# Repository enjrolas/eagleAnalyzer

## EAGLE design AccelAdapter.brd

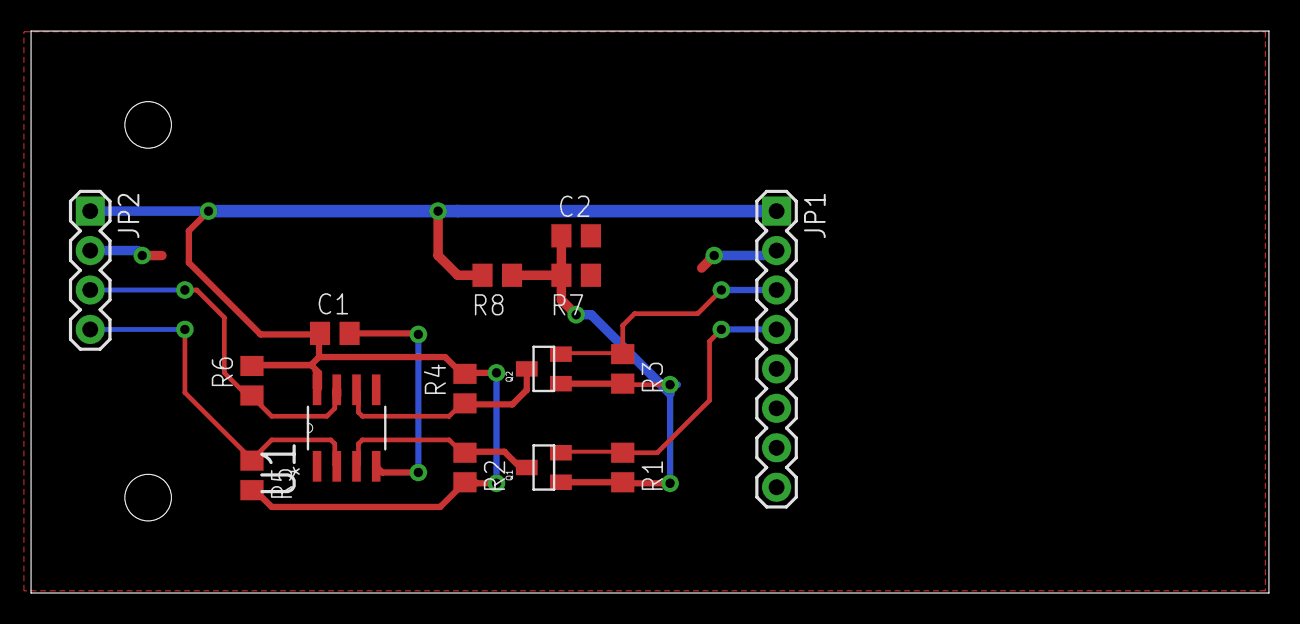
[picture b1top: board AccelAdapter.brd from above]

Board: 2 copper layers, 79.7 x 36.2 mm, 15 parts (0 on the bottom side), 9 nets.

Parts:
C1, C2: .1uF; C0805
JP1: Accel; 1X08
JP2: I2CExt; 1X04
Q1, Q2: MOSFET-NCHANNELBSS138; SOT23
R1, R2, R3, R4: 10k; R0805
R5, R6: 470R; R0805
R7: 330R; R0805
R8: 169R; R0805
U1: P82B715D; SOIC127P600X175-8N

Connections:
+3V3: C2.1, Q1.1, Q2.1, R1.2, R3.2, R7.2, R8.1
+5V: C1.1, JP1.1, JP2.1, R2.2, R4.2, R5.2, R6.2, R8.2, U1.8
GND: C1.2, C2.2, JP1.2, JP2.2, R7.1, U1.4
HSCL: Q2.3, R4.1, U1.6
HSDA: Q1.3, R2.1, U1.3
LCL: JP2.3, R6.1, U1.7
LDA: JP2.4, R5.1, U1.2
SCL: JP1.3, Q2.2, R3.1
SDA: JP1.4, Q1.2, R1.1

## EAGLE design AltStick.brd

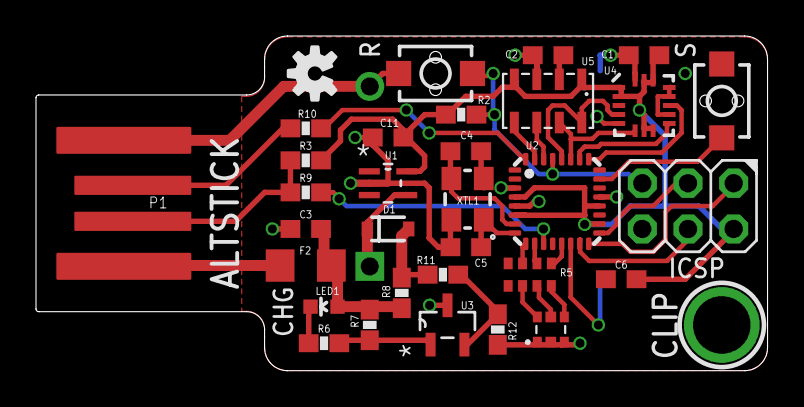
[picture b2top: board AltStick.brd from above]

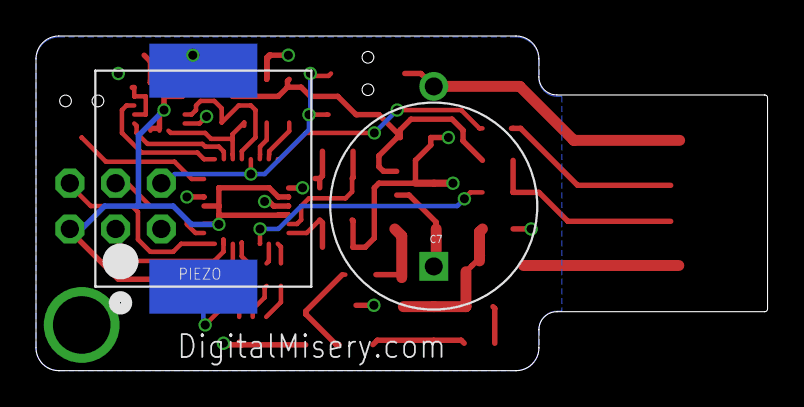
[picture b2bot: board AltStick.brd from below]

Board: 2 copper layers, 40.6 x 18.6 mm, 34 parts (2 on the bottom side), 34 nets.

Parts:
C1, C2, C6: 100nF; C0603
C3, C11: 1uF; C0603
C4, C5: 18pF; C0603
C7: 0.47F; KR-H11.5
D1: SOD-323
F2: R1206
ICSP: ICSP; 2X03
LED1: Green; LED-0603
LED2: RGBLEDSMT; 19-337
P1: USBPCB; USB-A-PCB
PIEZO: BUZZERSMD12X12; BUZZER-12X12-SMT
R2: 10k; 0603-RES
R3: 1.5k; 0603-RES
R5: 0603-ARV
R6: 1K; 0603-RES
R7: 1k; 0603-RES
R8: 20; 0603-RES
R9, R10: 30; 0603-RES
R11: 95k; 0603-RES
R12: 100k; 0603-RES
S1: RESET; TACTILE_SWITCH_SMD_2PIN_TINY
S2: BUTTON; TACTILE_SWITCH_SMD_2PIN_TINY
U1: TPS71533DCKR; SOT65P210X110-5N
U2: ATMEGA168MLF; MLF32
U3: TL431CDBZR; SOT95P237X112-3N
U4: LIS331; LGA16-3MM
U5: MPL3115A2LGA8; LGA8
U$2: OSHW-LOGOS; OSHW-LOGO-S
XTL1: 12MHz; CRYSTAL-SMD-3X2

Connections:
3.3V: C1.1, C6.1, C11.1, ICSP.2, R2.2, R3.1, U1.5, U2.4, U2.6, U2.18, U2.20, U4.1, U4.7, U4.8, U4.14, U4.15, U5.1, U5.4
ACC_I1: U2.25, U4.11
ACC_I2: U2.26, U4.9
ALT_I1: U2.30, U5.6
ALT_I2: U2.31, U5.5
D+: P1.USB_P, R10.2
D-: P1.USB_M, R3.2, R9.2
GND: C1.2, C2.2, C3.2, C4.2, C5.2, C6.2, C7.2, C11.2, ICSP.6, LED2.1, LED2.2, LED2.3, P1.GND, PIEZO.1, R12.1, S1.1, S2.2, U1.2, U2.3, U2.5, U2.21, U3.3, U4.5, U4.10, U4.12, U4.13, U4.16, U5.3, XTL1.2, XTL1.4
LED1: R5.7, U2.9
LED2: R5.6, U2.10
LED3: R5.5, U2.13
MISO: ICSP.1, U2.16
MOSI: ICSP.4, U2.15
unnamed: S2.1, U2.23
unnamed: F2.1, P1.5V
unnamed: LED2.4, R5.2
unnamed: LED2.5, R5.3
unnamed: LED1.C, R6.2
unnamed: R6.1, R7.1, U3.1
unnamed: R11.1, R12.2, U3.2
unnamed: C7.1, D1.1, U1.4
unnamed: D1.2, R8.2, R11.2
unnamed: C4.1, U2.7, XTL1.3
unnamed: C5.1, U2.8, XTL1.1
unnamed: LED2.6, R5.4
unnamed: C2.1, U5.2
PIEZO: PIEZO.2, U2.14
RD+: R10.1, U2.32
RD-: R9.1, U2.11
RESET: ICSP.5, R2.1, S1.2, U2.29
SCK: ICSP.3, U2.17
SCL: U2.28, U4.4, U5.8
SDA: U2.27, U4.6, U5.7
USBVCC: C3.1, F2.2, LED1.A, R7.2, R8.1

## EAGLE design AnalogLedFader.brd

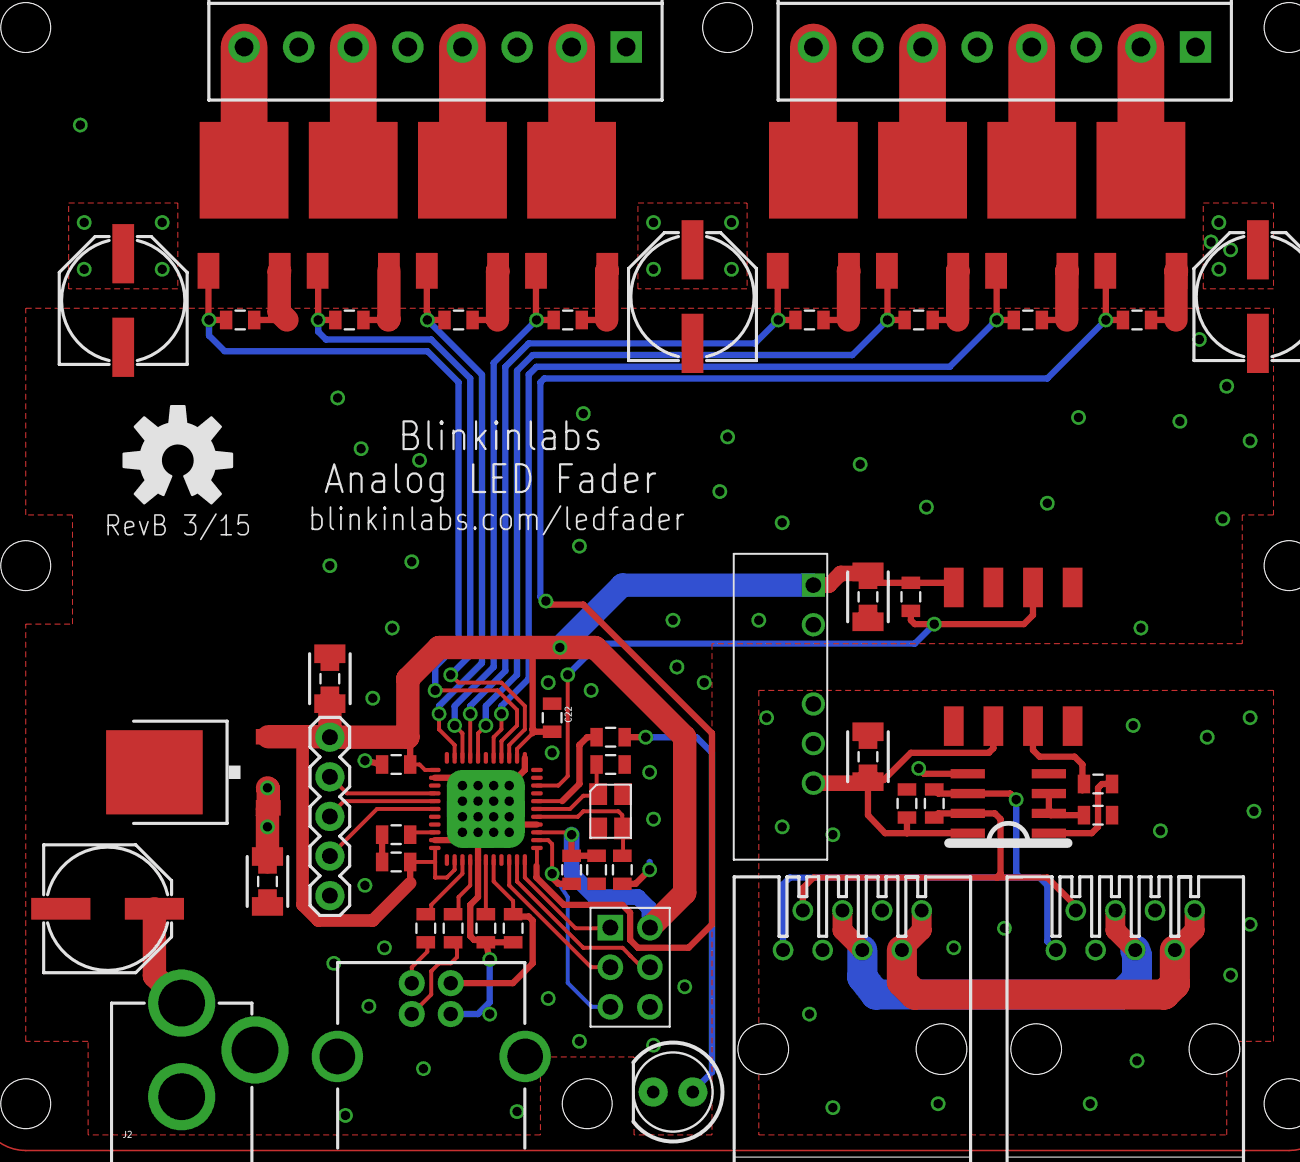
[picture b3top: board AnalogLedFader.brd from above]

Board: 2 copper layers, 62 parts (0 on the bottom side), 46 nets.

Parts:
C1, C2: 16pf; 0805
C3, C5, C6, C7, C12, C22: 100nF; 0805
C4, C8, C15: 1uF; 0805
C9: 4.7uF; 0805
C10: 10uF; 0805
C11: .3uF; 0805
C13: .3uF; 1210
C14: 100nF; 1210
C16: 4.7uF; 1210
C17: 10uF; 1210
C23, C24, C25, C26: PANASONIC_E
IC2: 7805DT; TO252
J1, J3: RS485; 520426-4
J2: POWER_JACKPTH; POWER_JACK_PTH
JP2, JP3: SCREWTERMINAL-3.5MM-8
JP6: 1X05
LED1: LED5MM
Q1: 16MHz 10ppm; XS3225
R1: 180 DNP; 0805
R2: 10k; 0805
R3, R4, R7, R9, R10, R13, R14, R15, R16: 10K; 0805
R5, R6: 22; 0805
R8, R11, R12: 470; 0805
U1: ARDUINO_LEONARDO-REV3B_SMARTPRJ_ATMEGA32U4-XUMU; ARDUINO_LEONARDO-REV3B_SMARTPRJ_QFN44ML7X7
U2: SN75176ASOIC; SO08
U$1, U$3, U$4, U$5, U$6, U$7, U$8, U$9: N_MOSFET; TO252
U$2: 2X3HEADER
U$10: DC_DC_ISOLATED_0505; IB_XLS-1W
U$12: 6N137; 8_SOIC
U$13: OSHW-LOGO-L
X1: USBPTH; USB-B-PTH

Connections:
5V_ISO: C7.2, C10.2, C17.1, U2.8, U$10.P$5, U$12.P$2
A1: JP6.2, U1.37
A2: JP6.3, U1.38
A3: JP6.4, U1.39
CONNECT_ME: R2.1, U2.2, U2.3
GND: C1.1, C2.1, C3.1, C4.1, C5.1, C6.1, C8.1, C9.1, C11.1, C12.1, C13.2, C14.2, C15.1, C16.2, C22.1, C23.-, C24.-, C25.-, C26.-, IC2.3, J2.GND, J2.GNDBREAK, JP6.5, LED1.K, R3.1, R7.1, R9.1, R10.1, R13.1, R14.1, R15.1, R16.1, U1.5, U1.15, U1.23, U1.35, U1.43, U1.PAD@1, U1.PAD@2, U1.PAD@3, U1.PAD@4, U1.PAD@5, U1.PAD@6, U1.PAD@7, U1.PAD@8, U1.PAD@9, U1.PAD@10, U1.PAD@11, U1.PAD@12, U1.PAD@13, U1.PAD@14, U1.PAD@15, U1.PAD@16, U$1.P$2, U$2.P$6, U$3.P$2, U$4.P$2, U$5.P$2, U$6.P$2, U$7.P$2, U$8.P$2, U$9.P$2, U$10.P$2, U$12.P$5, X1.GND
GND_ISO: C7.1, C10.1, C17.2, J1.7, J1.8, J3.7, J3.8, R2.2, U2.5, U$10.P$3, U$10.P$4
LED: R8.2, U1.18
MISO: U1.11, U$2.P$1
MOSI: U1.10, U$2.P$4
unnamed: R6.1, X1.D-
unnamed: C1.2, Q1.P$3, U1.16
unnamed: R5.1, X1.D+
unnamed: R5.2, U1.4
unnamed: C2.2, Q1.P$1, U1.17
unnamed: R6.2, U1.3
unnamed: LED1.A, R8.1
unnamed: C4.2, U1.6
unnamed: C8.2, U1.7, X1.VBUS
unnamed: C15.2, U1.42
unnamed: R11.1, U$12.P$3
OUT0: JP2.2, U$1.P$3
OUT1: JP2.4, U$3.P$3
OUT2: JP2.6, U$4.P$3
OUT3: JP2.8, U$5.P$3
OUT4: JP3.2, U$6.P$3
OUT5: JP3.4, U$7.P$3
OUT6: JP3.6, U$8.P$3
OUT7: JP3.8, U$9.P$3
PWM0: R10.2, U1.12, U$1.P$1
PWM1: R9.2, U1.27, U$3.P$1
PWM2: R7.2, U1.29, U$4.P$1
PWM3: R3.2, U1.30, U$5.P$1
PWM4: R13.2, U1.31, U$6.P$1
PWM5: R14.2, U1.32, U$7.P$1
PWM6: R15.2, U1.25, U$8.P$1
PWM7: R16.2, U1.26, U$9.P$1
RESET: R4.1, U1.13, U$2.P$5
RS485A: J1.1, J3.1, R1.1, U2.6
RS485B: J1.2, J3.2, R1.2, U2.7
RX: R12.1, U1.20, U$12.P$6
RX_ISO: R11.2, U2.1
SCK: U1.9, U$2.P$3
VCC: C3.2, C5.2, C6.2, C9.2, C12.2, C14.1, C16.1, C22.2, IC2.2, JP6.1, R4.2, R12.2, U1.2, U1.14, U1.24, U1.34, U1.44, U$2.P$2, U$10.P$1, U$12.P$8
VMOT: J1.4, J1.5, J3.4, J3.5
V_IN: C11.2, C13.1, C23.+, C24.+, C25.+, C26.+, IC2.1, J2.PWR, JP2.1, JP2.3, JP2.5, JP2.7, JP3.1, JP3.3, JP3.5, JP3.7

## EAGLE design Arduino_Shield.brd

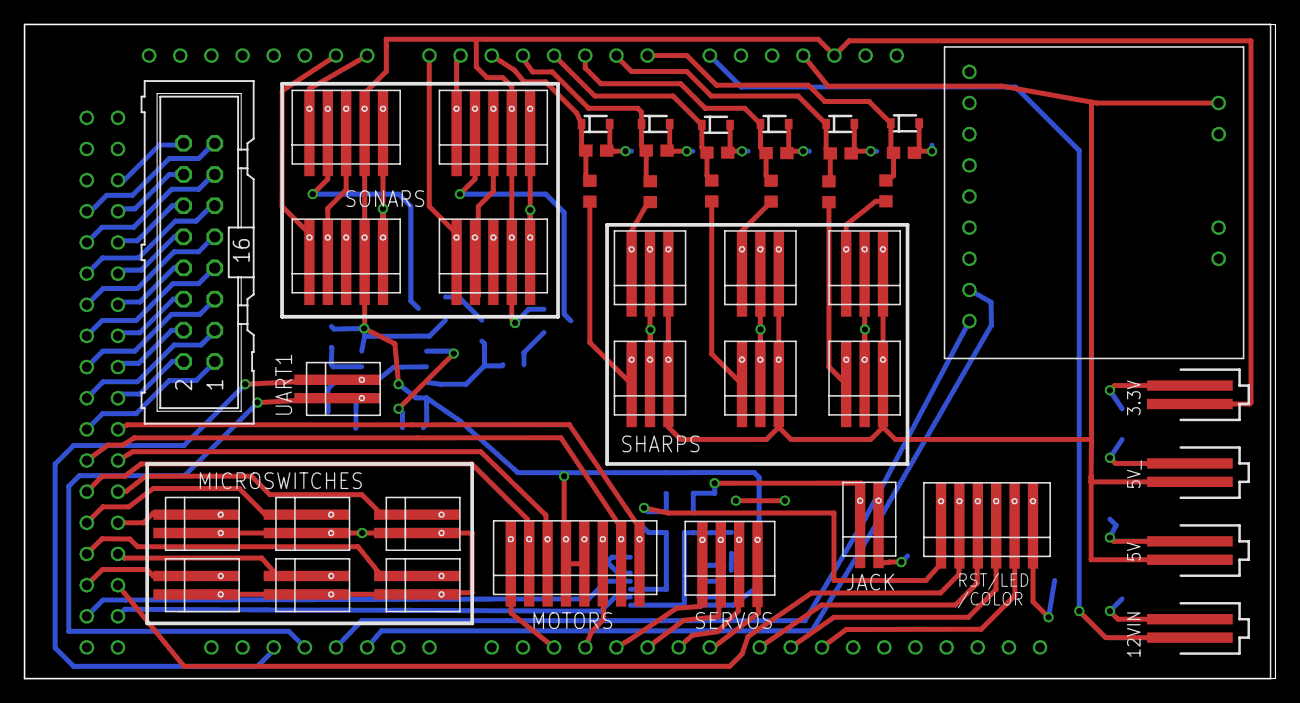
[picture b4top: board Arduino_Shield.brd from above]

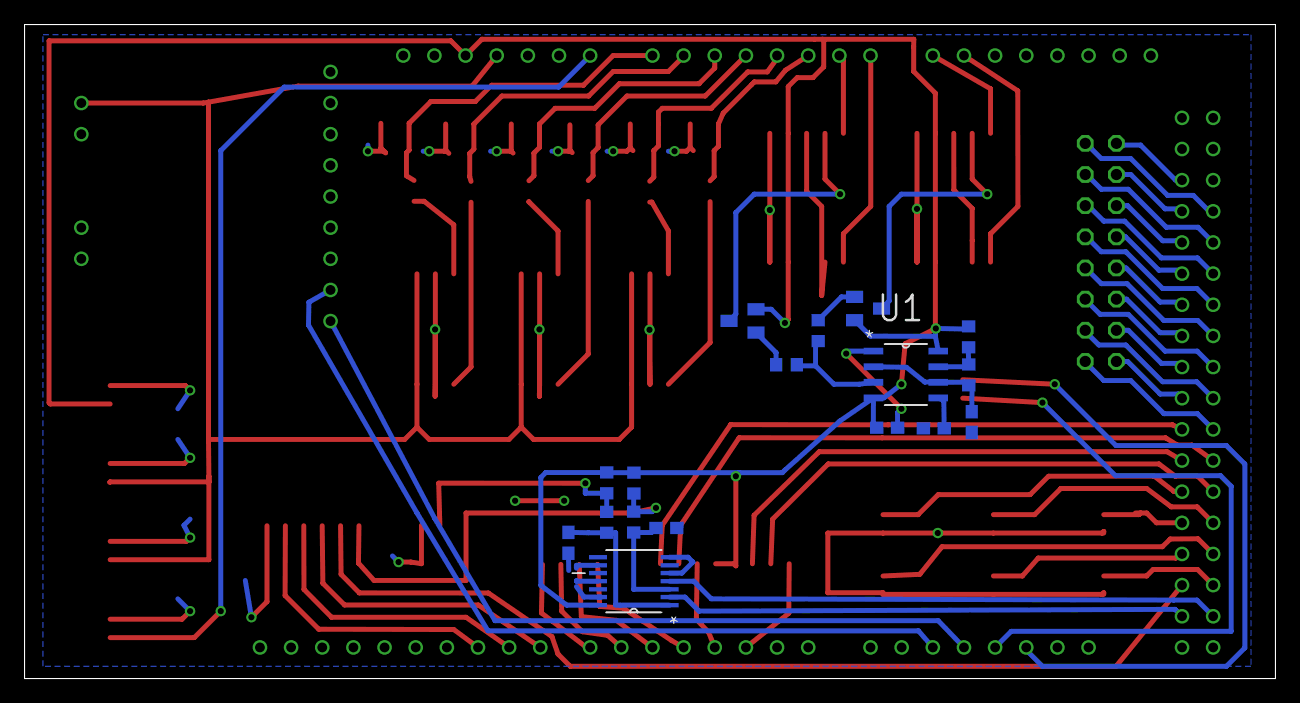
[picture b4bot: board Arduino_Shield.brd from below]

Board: 2 copper layers, 102.0 x 53.3 mm, 63 parts (17 on the bottom side), 76 nets.

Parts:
3.3V, 5V, 5V_, 12VIN: 87438-02
C1, C2, C4, C5, C6, C7, C8, C9: 0.1uF; C0603
C3: 1uF; C0603
C10, C11: 10uF; C0603
FPGA: ML16
JACK: 87437-0243
MOTORS: 87437-0843
Q1, Q2: BC857B; SOT23
R1, R2, R3, R4, R5, R6, R7, R10, R11, R12: 10K; R0603
R8, R9: 1K; R0603
RA: 330K; R0603
RB: 3.3K; R0603
RST/LED/COLOR: 87437-0643
SERVOS: 87437-0443
SHARP1, SHARP2, SHARP3, SHARP4, SHARP5, SHARP6: 87437-0343
SONAR_BL: 87437-0543
SONAR_BR: 87437-0543
SONAR_FL: 87437-0543
SONAR_FR: 87437-0543
U1: TLC555; SOIC127P600X175-8N
U2: SN74HC14PW; SOP65P640X120-14N
U$1: ARDUINO-DUE
U$2, U$3, U$4, U$5, U$6, U$7: ZENER_3.3V; SOD-323
UART1: 87437-0243
UM6: UM6
USW1, USW2, USW3, USW4, USW5, USW6: 87437-0243

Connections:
3.3VCC: 3.3V.1, C8.1, MOTORS.P$4, MOTORS.P$5, Q1.2, Q2.2, R7.2, R10.2, RA.2, SONAR_BL.P$4, SONAR_BR.P$4, SONAR_FL.P$4, SONAR_FR.P$4, U1.4, U1.8, U2.14, U$1.3.3V
5VCC: 5V.1, 5V_.1, SHARP1.P$3, SHARP2.P$3, SHARP3.P$3, SHARP4.P$3, SHARP5.P$3, SHARP6.P$3, U$1.5V3, UM6.P$10
12VIN: 12VIN.1, U$1.VIN
COLOR: RST/LED/COLOR.P$2, U$1.24
GND: 3.3V.2, 5V.2, 5V_.2, 12VIN.2, C1.1, C2.2, C3.2, C4.1, C5.1, C6.1, C7.1, C8.2, C9.1, C10.2, C11.2, JACK.P$2, RST/LED/COLOR.P$6, SHARP1.P$2, SHARP2.P$2, SHARP3.P$2, SHARP4.P$2, SHARP5.P$2, SHARP6.P$2, SONAR_BL.P$5, SONAR_BR.P$5, SONAR_FL.P$5, SONAR_FR.P$5, U1.1, U2.5, U2.7, U2.9, U2.11, U2.13, U$1.GND4, U$2.2, U$3.2, U$4.2, U$5.2, U$6.2, U$7.2, UM6.P$11, USW1.P$2, USW2.P$2, USW3.P$2, USW4.P$2, USW5.P$2, USW6.P$2
MOTOR1_BREAK: MOTORS.P$3, U$1.32
MOTOR1_DIR: MOTORS.P$2, U$1.31
MOTOR1_PWM: MOTORS.P$1, U$1.PWM2
MOTOR2_BREAK: MOTORS.P$8, U$1.34
MOTOR2_DIR: MOTORS.P$7, U$1.33
MOTOR2_PWM: MOTORS.P$6, U$1.PWM3
unnamed: RST/LED/COLOR.P$3, U$1.PWM8
unnamed: SERVOS.P$1, U$1.PWM4
unnamed: SERVOS.P$2, U$1.PWM5
unnamed: SERVOS.P$3, U$1.PWM6
unnamed: SERVOS.P$4, U$1.PWM7
unnamed: U$1.TX1, UART1.P$2
unnamed: U$1.RX1, UART1.P$1
unnamed: U2.2, U$1.22
unnamed: RST/LED/COLOR.P$4, U$1.PWM9
unnamed: RST/LED/COLOR.P$5, U$1.PWM10
unnamed: U2.4, U$1.23
unnamed: JACK.P$1, R7.1, R8.2
unnamed: C3.1, RB.1, U1.2, U1.6
unnamed: C2.1, U1.5
unnamed: RA.1, RB.2, U1.7
unnamed: R11.2, R12.2, U1.3
unnamed: Q2.1, R12.1
unnamed: Q1.1, R11.1
unnamed: SONAR_FL.P$3, SONAR_FR.P$2
unnamed: SONAR_BL.P$3, SONAR_BR.P$2
unnamed: FPGA.1, U$1.35
unnamed: Q1.3, SONAR_FL.P$2
unnamed: Q2.3, SONAR_BL.P$2
unnamed: FPGA.2, U$1.36
unnamed: FPGA.3, U$1.37
unnamed: FPGA.4, U$1.38
unnamed: FPGA.5, U$1.39
unnamed: FPGA.6, U$1.40
unnamed: FPGA.7, U$1.41
unnamed: FPGA.8, U$1.42
unnamed: FPGA.9, U$1.43
unnamed: FPGA.10, U$1.44
unnamed: FPGA.11, U$1.45
unnamed: FPGA.12, U$1.46
unnamed: FPGA.13, U$1.47
unnamed: FPGA.14, U$1.48
unnamed: FPGA.15, U$1.49
unnamed: FPGA.16, U$1.50
unnamed: R5.1, SHARP2.P$1
unnamed: R4.1, SHARP3.P$1
unnamed: R3.1, SHARP4.P$1
unnamed: R2.1, SHARP5.P$1
unnamed: R1.1, SHARP6.P$1
unnamed: C10.1, R8.1, U2.1
unnamed: R6.1, SHARP1.P$1
unnamed: C11.1, R9.1, U2.3
RST: R9.2, R10.1, RST/LED/COLOR.P$1
SHARP1: C1.2, R6.2, U$1.A0, U$2.1
SHARP2: C4.2, R5.2, U$1.A1, U$3.1
SHARP3: C5.2, R4.2, U$1.A2, U$4.1
SHARP4: C6.2, R3.2, U$1.A3, U$5.1
SHARP5: C7.2, R2.2, U$1.A4, U$6.1
SHARP6: C9.2, R1.2, U$1.A5, U$7.1
SONAR_BL: SONAR_BL.P$1, U$1.A8
SONAR_BR: SONAR_BR.P$1, U$1.A9
SONAR_FL: SONAR_FL.P$1, U$1.A6
SONAR_FR: SONAR_FR.P$1, U$1.A7
UM6_RX: U$1.TX2, UM6.P$2
UM6_TX: U$1.RX2, UM6.P$1
USW1: U$1.25, USW1.P$1
USW2: U$1.26, USW2.P$1
USW3: U$1.27, USW3.P$1
USW4: U$1.28, USW4.P$1
USW5: U$1.29, USW5.P$1
USW6: U$1.30, USW6.P$1

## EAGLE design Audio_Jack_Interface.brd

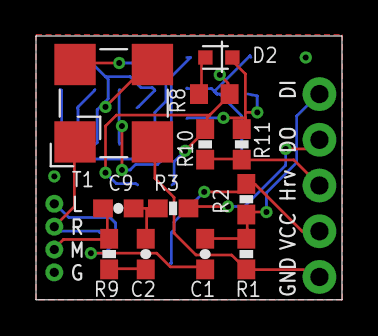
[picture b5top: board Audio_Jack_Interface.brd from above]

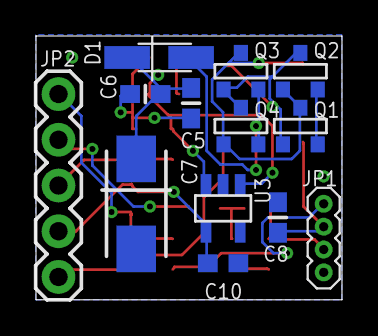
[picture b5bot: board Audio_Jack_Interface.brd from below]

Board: 2 copper layers, 17.0 x 14.7 mm, 25 parts (13 on the bottom side), 14 nets.

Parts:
C1: 0.1 uF; 0603-CAP
C2: 4.7nF; 0603-CAP
C5: 1uF; C0603
C6: 10uF; C0603
C7: CP6032; CT6032
C8: 2.2u; C0603
C9: 10uF; 0603-CAP
C10: 10u; C0603
D1: DIODE; MINIMELF
D2: LED-0603
JP1: 1X04-1.27MM
JP2: 1X05
Q1, Q2, Q3, Q4: SOT-23
R1, R2: 100k; 0603-RES
R3: 10k; 0603-RES
R8: 698; R0603
R9: 1k; 0603-RES
R10: 3M; 0603-RES
R11: 1M; 0603-RES
T1: LPR6235
U3: MIC5231; SOT23-5

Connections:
GND: C2.2, C5.2, C6.2, C7.-, C8.2, C10.2, D2.C, JP1.1, JP2.1, Q1.2, Q2.2, R1.1, R9.2, R11.1, T1.2, U3.2
LEFT: C1.1, JP1.4
MIC: C9.2, JP1.2, R9.1
unnamed: C1.2, JP2.5, R1.2, R2.1
unnamed: JP2.3, R10.1, R11.2
unnamed: JP2.4, R3.2
unnamed: Q1.1, Q2.3, Q3.1, Q4.3, T1.4
unnamed: Q1.3, Q2.1, Q3.3, Q4.1, T1.3
unnamed: D2.A, R8.2
unnamed: C2.1, C9.1, R3.1
unnamed: D1.A, Q3.2, Q4.2
RIGHT: C8.1, JP1.3, T1.1
VCC: C10.1, JP2.2, R2.2, U3.4
VHARVEST: C5.1, C6.1, C7.+, D1.C, R8.1, R10.2, U3.1, U3.3

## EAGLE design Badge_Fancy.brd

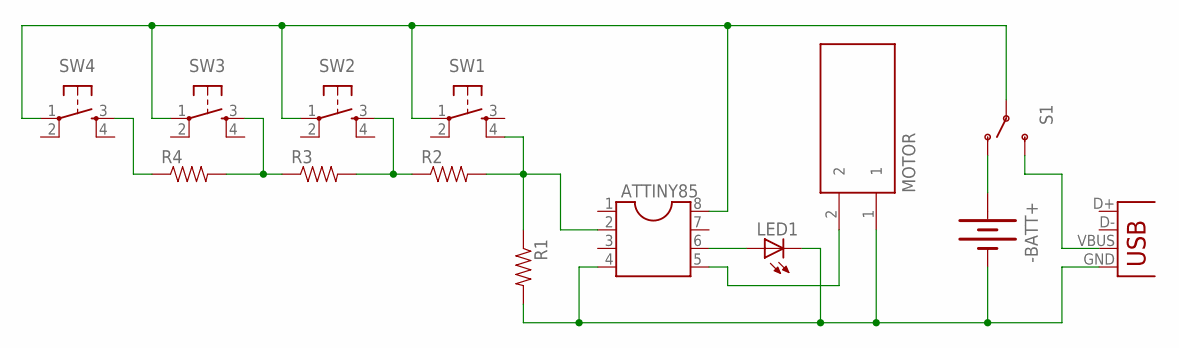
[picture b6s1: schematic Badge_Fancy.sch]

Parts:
-BATT+: BATTERY245MM; BATTCON_245MM
ATTINY85: DIL8S; SOCKET-08
LED1: LEDCHIPLED_0805; CHIPLED_0805
MOTOR: VIB-MOTOR
R1, R2, R3, R4: RESISTOR2010; R2010
S1: SWITCH-SPSTSMD; AYZ0202
SW1, SW2, SW3, SW4: TAC_SWITCHPTH; TACTILE-PTH
X2: USBSMD; USB-MINIB

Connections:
+3V: ATTINY85.8, S1.2, SW1.1, SW2.1, SW3.1, SW4.1
GND: -BATT+.2 (-), ATTINY85.4, LED1.C, MOTOR.1, R1.2, X2.GND
unnamed: ATTINY85.5, MOTOR.2
unnamed: -BATT+.1 (+), S1.1 (O)
unnamed: S1.3 (S), X2.VBUS
unnamed: ATTINY85.2, R1.1, R2.2, SW1.4
unnamed: ATTINY85.6, LED1.A
unnamed: R4.1, SW4.3
unnamed: R3.1, R4.2, SW3.3
unnamed: R2.1, R3.2, SW2.3

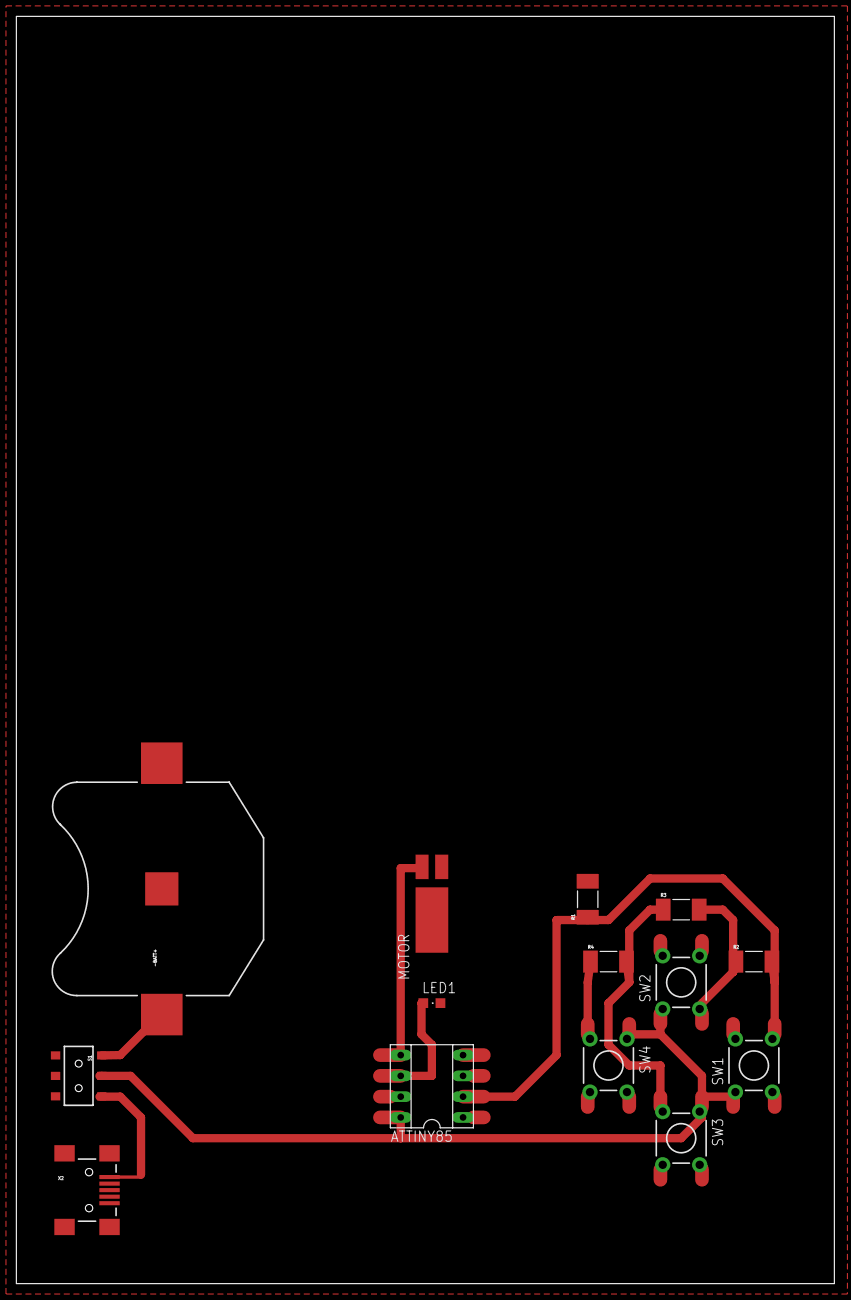
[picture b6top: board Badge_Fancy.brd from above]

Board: 2 copper layers, 100.0 x 154.9 mm, 14 parts (0 on the bottom side), 10 nets.

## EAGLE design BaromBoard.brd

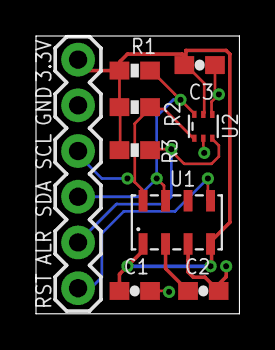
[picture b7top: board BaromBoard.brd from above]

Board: 2 copper layers, 11.3 x 15.4 mm, 9 parts (0 on the bottom side), 7 nets.

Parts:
C1, C2, C3: 1uF; 0603-CAP
JP1: 1X06
R1, R2, R3: 0603-RES
TMP102: TMP102; SOT563
U1: MPL115A; LGA8

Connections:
3.3V: C1.1, C3.1, JP1.1, R1.2, R2.2, R3.1, TMP102.5, U1.1, U1.4
ALERT: JP1.5, R3.2, TMP102.3
GND: C1.2, C2.2, C3.2, JP1.2, TMP102.2, TMP102.4, U1.3
MPL_RST: JP1.6, U1.5
unnamed: C2.1, U1.2
SCL: JP1.3, R2.1, TMP102.1, U1.8
SDA: JP1.4, R1.1, TMP102.6, U1.7

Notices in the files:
parts and their libraries:
SparkFun-DiscreteSemi: Licensing: CC v3.0 Share-Alike You are welcome to use this library for commercial purposes.
bone: ©2009 ROFA.cz - modified by Greg Larmore ‹larmoreg@gmail.com›
